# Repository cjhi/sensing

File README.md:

# Sensing

Repository for all Olin Rocketry hardware and firmware.

The purpose of the avionics system is to determine when to deploy the drogue and main chutes, and to send the signal to do so to the recovery system. The flight computer contains several sensors to help detect apogee, and a microcontroller to read and process the data and send the signal.

The avionics system consists of

- a commercial-off-the-shelf (COTS) flight computer;
- a student-designed flight computer, which includes sensors, microcontroller, GPS, and radio; and
- a student-designed battery management system (BMS).

The COTS computer is a **\_** model. It has its own batteries, sensors, and radio and can trigger the recovery system independently. It is intended as a backup and is required by IREC competition rules (partly so they have a reliable altitude measurement for the competition). The BMS is described on the Power Management subteam page. It can suppy a steady 3.3V current up to about 1000 mA to the student-designed flight computer board.

**The flight computer consists of a Teensy 3.6 microcontroller and various sensors.**

- The [Teensy 3.6](https://www.pjrc.com/teensy/card9a_rev1.pdf) is computationally powerful enough for complex data processing, has many interrupt pins, and many pins in general for connecting multiple sensors. It also has a built-in SD card reader. The decision to use it was made before the Fall 2020 semester; other options were considered and may be viable for future iterations. The main drawback of the Teensy 3.6 is its cost, at around $30. This makes having multiple prototypes very expensive, especially if we want to distribute copies to team members living in separate places.
- We considered 3 different inertial measurement units (IMUs, or accelerometers):
  - [ADXL345](https://www.analog.com/media/en/technical-documentation/data-sheets/ADXL345.pdf) is a very common 3-axis accelerometer. It is widely available and was already in stock from JLC, the company manufacturing our board. This means our boards will have the ADXL345 already populated when it is shipped to us, a bonus.
  - [BMI088](https://download.mikroe.com/documents/datasheets/BMI088_Datasheet.pdf) is a 6-axis accelerometer and gyroscope (axes 4-6 are angular acceleration).
  - [BNO055](https://cdn-shop.adafruit.com/datasheets/BST_BNO055_DS000_12.pdf) is a 9-axis accelerometer, relative, and absolute gyroscope (axes 7-9 are absolute orientation).

We designed our Rev1 PCB to hold all three IMUs, so that we could test all of them at once. However, as of ordering time in January, the BMI088 and BNO055 were out of stock at Digikey and Mouser, so these were never tested.

- [MPL3115A2](https://www.nxp.com/docs/en/data-sheet/MPL3115A2.pdf) is a barometer calibrated to provide altimetry. It is the most important sensor, as it allows us to determine our absolute altitude. Our simplest apogee detection is triggered by a certain number of consecutive decreasing altitude measurements.
- Header pins for the [Adafruit Ultimate GPS Breakout (Version 3)](https://www.adafruit.com/product/746?__hstc), a $40 complete GPS module.
- Header pins for the [RFM9X LoRa Packet Radio Breakout](https://learn.adafruit.com/adafruit-rfm69hcw-and-rfm96-rfm95-rfm98-lora-packet-padio-breakouts/arduino-wiring), the currenty preferred radio (see Communications subteam page).

**Rev 1 Testing Update: Spring 2021**

The sensors on Rev1 (the ADXL345 accelerometer and the MPL3115A2 barometer) work, and the data can be read over I2C. The current data format is a csv file with time since launch, x, y, and z acceleration, pressure, altitude, and temperature. The readings from the accelerometer have very little noise when at rest (the only test performed so far - others to follow soon). The barometer has some issues. First of all, it has an offset of about 1.7 atmospheres. When those 1.7 atm are subtracted out, however, it provides high precision and sensitivity. The altitude readings are off by the same offset, as I believe they are calculated from the barometer reading anyway. The temperature has some 20 degrees F offset and significant drift of 2-5 degrees F over a few minutes. More testing to follow.

I looked at the specs and realized that the ADXL345 and MPL3115A2 together consume less than 3 mA of current at their max. Since the Teensy can output 250 mA through those pins, I don’t see why to use an external power source; we can just use the 3.3V pins on the Teensy.
The tests I have done have been using the 3.3V pin as a power source.

**Tests performed 3/26/2021:**

**Power supply test:** Get an external power supply and give 3.3V to the power inputs. Test the test points and the Teensy’s Vin pin. Test data logging onto SD card. Test sensors connected only to external power supply vs. connected to Teensy 3.3V pin vs. connected to both.

**Results:**
The transistor part of the Rev1 power management circuit did not work. For some reason, there was always only ~0.6V on both the gate and drain pins, and so 0.6V on the rest of the PCB. I tried several pin configurations and nothing helped. It worked fine when I bypassed the transistor and powered 3.3V to both the Teensy and the PCB.
The Teensy could not write to the SD card when the PCB and Teensy were powered independently; it only works when the rest of the PCB is powered through the Teensy’s dedicated 3.3V pin. Therefore, I recommend just using the Teensy’s 3.3V pin to power the sensors.

In this case, I suggest the voltage supplied by the BMS should be 3.6V instead of 3.3V, so that the linear voltage regulator on the Teensy can effectively supply the 3.3V to the sensors. Voltage regulators necessariy have a small voltage drop across them, although I came across a [source](https://forum.pjrc.com/threads/55789-Power-Teensy-3-6-with-lipo-battery?p=203568&viewfull=1#post203568) that says the Teensy will bypass its voltage regulator if the voltage is too low, so there is not necessarily an issue.

**MPL3115A2 Accuracy Test:** Take the Rev1 board up and down the stairs of the MAC building 2 times and measure altitude difference.

**Results:**
The readings are inaccurate, yet very precise. The pressure has reads on the order of 200 kPa, which is double what is expected (1 atmosphere is about 100 kPa), and the temperature reads 90 degrees F in a 70 degree room. Yet after the offset is subtracted, the sensor tracks changes in height of less than 20 feet (the distance between floors in the MAC, and the highest resolution analyzed) quite well. The graph below shows the corrected elevation and temperature over the course of my trip up and down the stairs of the MAC, then outside onto the great lawn and up to the 4th floor of West Hall. There is some drift over time as it sat on my desk after “landing,” on the order of 20 feet over 20 minutes. This is worrying, but it will likely not be a problem during a launch lasting a few minutes.

**Developing the Rev 2 board**

With the ADXL345 and MPL3115A2 sensors confirmed to work, the main objective of the Rev 2 board is to make it fit into the avionics bay. The final board is 80mm tall by 72mm wide and has a mounting hole in each corner. The power supply transistor circuit has been replaced with a power multiplexer, a zener diode was added for overvoltage protection, and the power from the BMS goes directly into the Vin pin on the Teensy; the sensors and other circuitry are powered by the Teensy's 3.3V pin as discussed above. Additionally, 5 debugging LEDs, one power LED, and a [buzzer](https://www.digikey.com/en/products/detail/mallory-sonalert-products-inc/PT-1340P-P10-PQ/4996070) have also been added and are controlled by spare digital pins on the Teensy. A 10uF capacitor was added between the power and ground pins of the radio upon testing by the Communications team.

The board has been ordered from JLC and will arrive within a couple days.

## Guide to creating PCBs

**The process for creating the flight computer PCB has multiple stages:**
  1. Components are selected, including the microcontroller and sensors.
  2. Schematics are created for each sensor individually. This mainly involves copying the circuit diagram from the datasheets for each sensor. Every sensor needs at least two capacitors for its power source, and some require external pull-up resistors, for example. The BNO055 is connected to an external crystal oscillator. It’s also a good idea to add test points (basically large, labelled vias) for debugging purposes. We tried to add a test point to every trace on the schematic that would not be directly connected to the microcontroller (because we can access those traces directly through the microcontroller’s pins). 
  3. For the Rev1 board, footprints for the BNO055 and MPL3115A2 were created by copying the dimensions given by the datasheets. The other footprints were downloaded from snapeda.com. In reality, the only reason to create them manually is to get practice with KiCAD, which is why it was done this way for two of the sensors; in future, snapeda.com likely has all the footprints we will need, without the possibility of human error.*
  4. At this stage, layouts are also created for the supporting circuitry surrounding each sensor individually. These layouts will be manually recreated later, but it is easier to go through a few iterations to find the optimal footprint placements now, before all the layouts are combined on one board.
  5. Now, all of the individual schematics are moved into one place. This can be done in the KiCAD schematic editor (eeschema) by clicking File -> Append Schematic Sheet Content -> then navigate to the schematic to import and click Use Relative Path.
  6. Now all the schematics can be hooked up together; in this case it means connecting each sensor’s communication pins to the Teensy and power and ground to the power supply. A small circuit for regulating the power supply from the BMS, as well as header pins for the BMS and GPS and radio breakout boards are also added to this schematic.
  7. Review the schematics with the flight computer sub-team. Hopefully we have been checking in all along, but now is the last chance to make changes before a lot of work goes into the layout. After this, even small changes to the schematic can be very hard to implement in the layout without starting over.
  8. The layout of all the components for the final PCB is created. You cannot copy and paste the layouts created earlier for individual sensors, but you can follow the prior layouts as a guide. For the Rev1 board, we kept the components in the same relative orientation but did not pack them as closely together, to make debugging and potential fixes easier. During the layout process, it will probably make sense to swap the order of some pins connected to the microcontroller, in order to untangle the traces, or reduce the number of times traces have to cross over. Most pins on the Teensy 3.6 can function in the same way, so switching which pins are connected to which sensor is not a problem. Be careful not to switch the order of SCK and SDA; MISO and MOSI; or RX and TX; these pins are not interchangeable.
  9. It's a good idea to add filled zones on the front and back of the board. Having filled zones helps reduce signal noise and is standard practice. It also means there are fewer traces you have to draw. I usually make my filled zones be ground on both sides of the PCB, with an abundance of vias throughout the board to connect the front and back ground planes. Remember to press 'B' to redraw the zones in KiCAD.
  10. When the layout is done and reviewed, it is sent to JLC, our manufacturer. JLC can populate the PCB with basic components like capacitors, resistors, and even the ADXL345. They did not have any of the other sensors in stock, so we will solder those on campus. We will also solder header pins and large components like the power-regulating MOSFET transistor (which will be discontinued in Rev2).
  11. Next up is writing the firmware to test the sensors and hopefully getting some data!

\* In fact, I did make a very significant error while copying the footprint from the datasheet for both the BNO055 and the MPL3115. I copied the pads as they were shown in the datasheet, which was a bottom-up view. What matters for the layout is the top-down view (think about how the sensor sits on the PCB; you want to design the pads so they sit directly beneath the sensor). When you design the pads using the bottom-up view, you get a mirror image of how they are supposed to be. Moreover, since the footprints are often symmetrical, it can be impossible to tell you’ve made a mistake, until you realize that the pins things are supposed to be connected to are actually on the opposite side of the chip.

### Rev2 images

**Rev2 full schematic**

**Rev2 power supply**

**Rev2 layout**

**Rev2 3D model (front)**

**Rev2 3D model (back)**

### Rev1 images

**Rev1 full schematic**

**Rev1 power supply**

**Rev1 layout**

**Rev1 3D model (front)**

**Rev1 3D model (back)**

## Ordering PCBs From JLCPCB

For ordering the boards, go to JLCPCB.com (https://jlcpcb.com/RAT), and click on "Quote Now" button.

JLCPCB (ShenzhenJLC Electronics Co., Ltd.), is the largest PCB prototype enterprise in China, and a high-tech manufacturer specializing in quick PCB prototype and small-batch PCB production. You can order a minimum of 5 PCBs for just $2.

First: Upload the gerber files for the board by clicking the "Add gerber file" button. You’ll notice a message at the bottom if the file is successfully uploaded.

A correctly uploaded gerber folder renders the board as follows:

Second: In order to get the board assembled (optional, based on the project requirements), select the "SMT Assembly option. It is important to select the side of the PCB that needs to be assembled, as well as the quantity for SMT. Press the "Confirm" button, then press the "Next" button.

Third: upload the BOM (Bill of Material) and CPL (Component Placement List) files and click the "Next" button. It is necessary to make sure that each of these files follow the jlcpcb specified BOM and CPL formats, respectively:

- [Sample BOM](https://jlcpcb.com//video/JLCSMT_Sample_BOM1.xlsx?_ga=2.42560357.1905056644.1612161700-100444678.1610257845)
- [Sample CPL](https://jlcpcb.com//video/JLCSMT_Sample_CPL1.xlsx?_ga=2.42560357.1905056644.1612161700-100444678.1610257845)
- [SMT FAQ's](https://support.jlcpcb.com/category/78-smt-assembly?_ga=2.42560357.1905056644.1612161700-100444678.1610257845)

Note: If there is an issue with the BOM/CPL formatting, the the page will keep erroring out until it is resolved.

Fourth: The parts are automatically detected through the uploaded BOM. They are also matched against jlcpcb's in-stock parts. It is important to go through each row and confirm if the auto-detected parts are the desired parts. Some parts will remain undetected if they cannot be assembled through SMT and require manual assembly post-deilvery.

Fifth: The website renders an assembled board using the CPL file. This feature can be used to review the placement of the components (including orientation). Once carefull reviewed, the next step is to download a list of parts remaining to be assembled towards the bottom of this page view. It is important to place an order for the remaining components to be manually assembled upon delivery.

Sixth: Click on the “Save to Cart” button. Then, click on the "Secure Checkout" button.

Last: Add the payment details and choose the suitable delivery method (this includes FedEx, DHL, and standard mail options). Then, place the order.

Optional: To review the production status of the board, click on the "Order History" button under username. Then, click on In Production > view progress to obtain timestamps for each of the production steps in real time.

**Design Reviews**

-11/9/2022

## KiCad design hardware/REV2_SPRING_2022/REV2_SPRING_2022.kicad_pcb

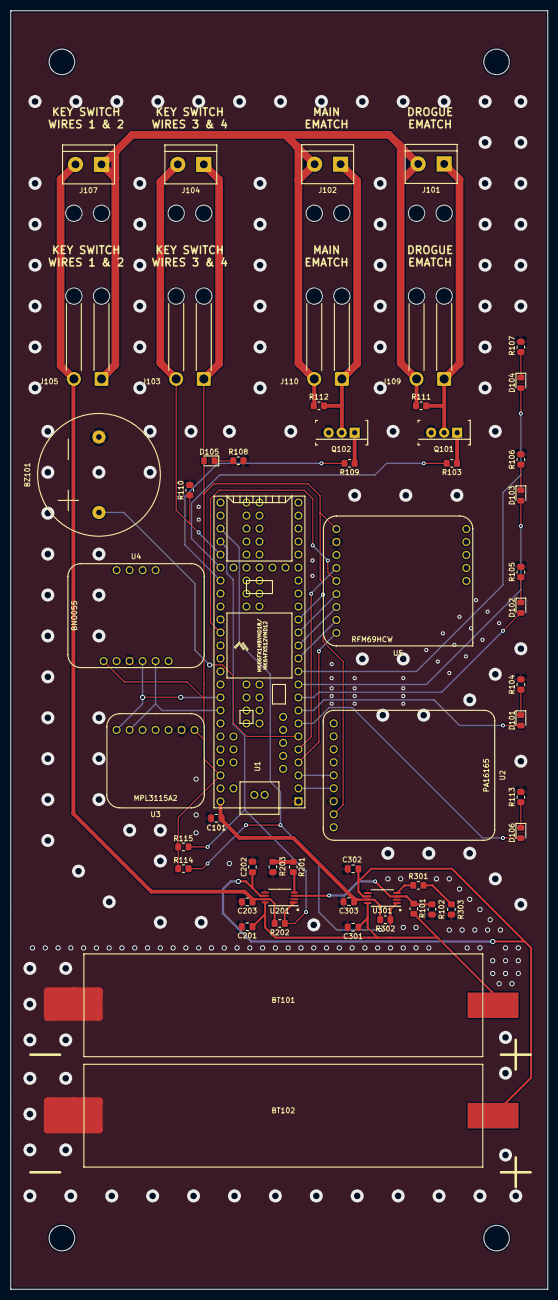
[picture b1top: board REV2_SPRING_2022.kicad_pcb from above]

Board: 2 copper layers, 105.0 x 250.0 mm, 54 parts (0 on the bottom side), 43 nets.

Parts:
BT101, BT102: Battery_Cell; MyBatteryHolder_MPD_BH-18650-PC2
BZ101: Buzzer; Large_Buzzer_24mmOD_14.8mmPinDistance_1.0mmPinDiameter
C101, C201, C202, C203, C301, C302, C303: C_0.1u; C_0805_2012Metric_Pad1.18x1.45mm_HandSolder
D101, D102, D103, D104, D105, D106: LED; LED_0805_2012Metric_Pad1.15x1.40mm_HandSolder
J101, J102, J104, J107: Screw_Terminal_01x02; TerminalBlock_bornier-2_P5.08mm
J103, J105, J109, J110: Conn_01x02_Female; SolderWire-1sqmm_1x02_P5.4mm_D1.4mm_OD2.7mm_Relief2x
Q101, Q102: Q_NMOS_GDS; TO-220-3
R101: R_15k; R_0805_2012Metric_Pad1.20x1.40mm_HandSolder
R102: R_4.7k; R_0805_2012Metric_Pad1.20x1.40mm_HandSolder
R103, R109, R110, R111, R112, R114, R115, R202, R302: R_10k; R_0805_2012Metric_Pad1.20x1.40mm_HandSolder
R104, R105, R106, R107, R108, R113: R_750; R_0805_2012Metric_Pad1.20x1.40mm_HandSolder
R201, R203, R301, R303: R_200; R_0805_2012Metric_Pad1.20x1.40mm_HandSolder
U1: Teensy3.6_All_Pins; Teensy35_36_All_Pins
U2: PA16165_Breakout
U3: MPL3115A2_Breakout
U4: BNO055_Breakout
U5: RFM69HCW_Breakout
U201, U301: TPS2113ADRBR; TSSOP-8_4.4x3mm_P0.65mm

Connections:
/3.3V: D105.2, J103.1, J104.1, R114.1, R115.1, U1.15, U1.51, U2.8, U3.1, U4.1, U5.1
/BAT1: BT101.1, C201.1, C301.1, R101.1, U201.8, U301.8
/BAT2: BT102.1, C202.1, C302.1, U201.6, U301.6
/BUZZER: BZ101.1, U1.6
/CS0: U1.12, U5.8
/E-MATCH_TRIGGER_1: R103.2, U1.35
/E-MATCH_TRIGGER_2: R109.2, U1.36
/EMATCH_1+: J101.1, J109.1, Q101.2, R111.2
/EMATCH_2+: J102.1, J110.1, Q102.2, R112.2
/KEY_SWITCH_DIGITAL: J103.2, J104.2, R110.1, U1.34
/LED_0: D106.2, U1.7
/LED_1: D101.2, U1.8
/LED_2: D102.2, U1.9
/LED_3: D103.2, U1.10
/LED_4: D104.2, U1.11
/MISO0: U1.14, U5.6
/MOSI0: U1.13, U5.7
/PWM: U1.4, U5.9
/RX1: U1.2, U2.6
/SCK: U1.40, U5.5
/SCL0: U1.46, U3.6, U4.5
/SCL2: U1.5, U5.4
/SDA0: U1.45, U3.7, U4.4
/TPS2113A for E-match/VSNS: R101.2, R102.1, U201.3, U301.3
/TPS_1_STAT: R114.2, R302.2, U1.32, U301.1
/TPS_2_STAT: R115.2, R202.2, U1.33, U201.1
/TX1: U1.3, U2.5
/V_EMATCH: J101.2, J102.2, J105.1, J107.1, J109.2, J110.2, R111.1, R112.1
/V_EMATCH_TO_KEY_SWITCH: C203.1, J105.2, J107.2, R202.1, U201.7
/V_TEENSY: C101.1, C303.1, R302.1, U1.53, U301.7
GND: BT101.2, BT102.2, BZ101.2, C101.2, C201.2, C202.2, C203.2, C301.2, C302.2, C303.2, Q101.3, Q102.3, R102.2, R104.2, R105.2, R106.2, R107.2, R108.2, R110.2, R113.2, R203.1, R303.1, U1.1, U1.39, U2.7, U3.2, U4.3, U5.2, U201.2, U201.5, U301.2, U301.5
unnamed: D101.1, R104.1
unnamed: D102.1, R105.1
unnamed: D103.1, R106.1
unnamed: D104.1, R107.1
unnamed: D105.1, R108.1
unnamed: D106.1, R113.1
unnamed: Q101.1, R103.1
unnamed: Q102.1, R109.1
unnamed: R201.1, R203.2
unnamed: R201.2, U201.4
unnamed: R301.1, R303.2
unnamed: R301.2, U301.4

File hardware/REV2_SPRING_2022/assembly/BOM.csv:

Comment,Designator,Footprint,LCSC Part #
C_0.1u,"C101, C201, C202, C203, C301, C302, C303, ",0805,C28233
LED,"D101, D102, D103, D104, D105, D106, ",0805,C2296
R_15k,"R101, ",0805,C17475
R_4.7k,"R102, ",0805,C17673
R_10k,"R103, R109, R110, R111, R112, R114, R115, R202, R302, ",0805,C17414
R_750,"R104, R105, R106, R107, R108, R113, ",0805,C17818
R_200,"R201, R203, R301, R303, ",0805,C17540

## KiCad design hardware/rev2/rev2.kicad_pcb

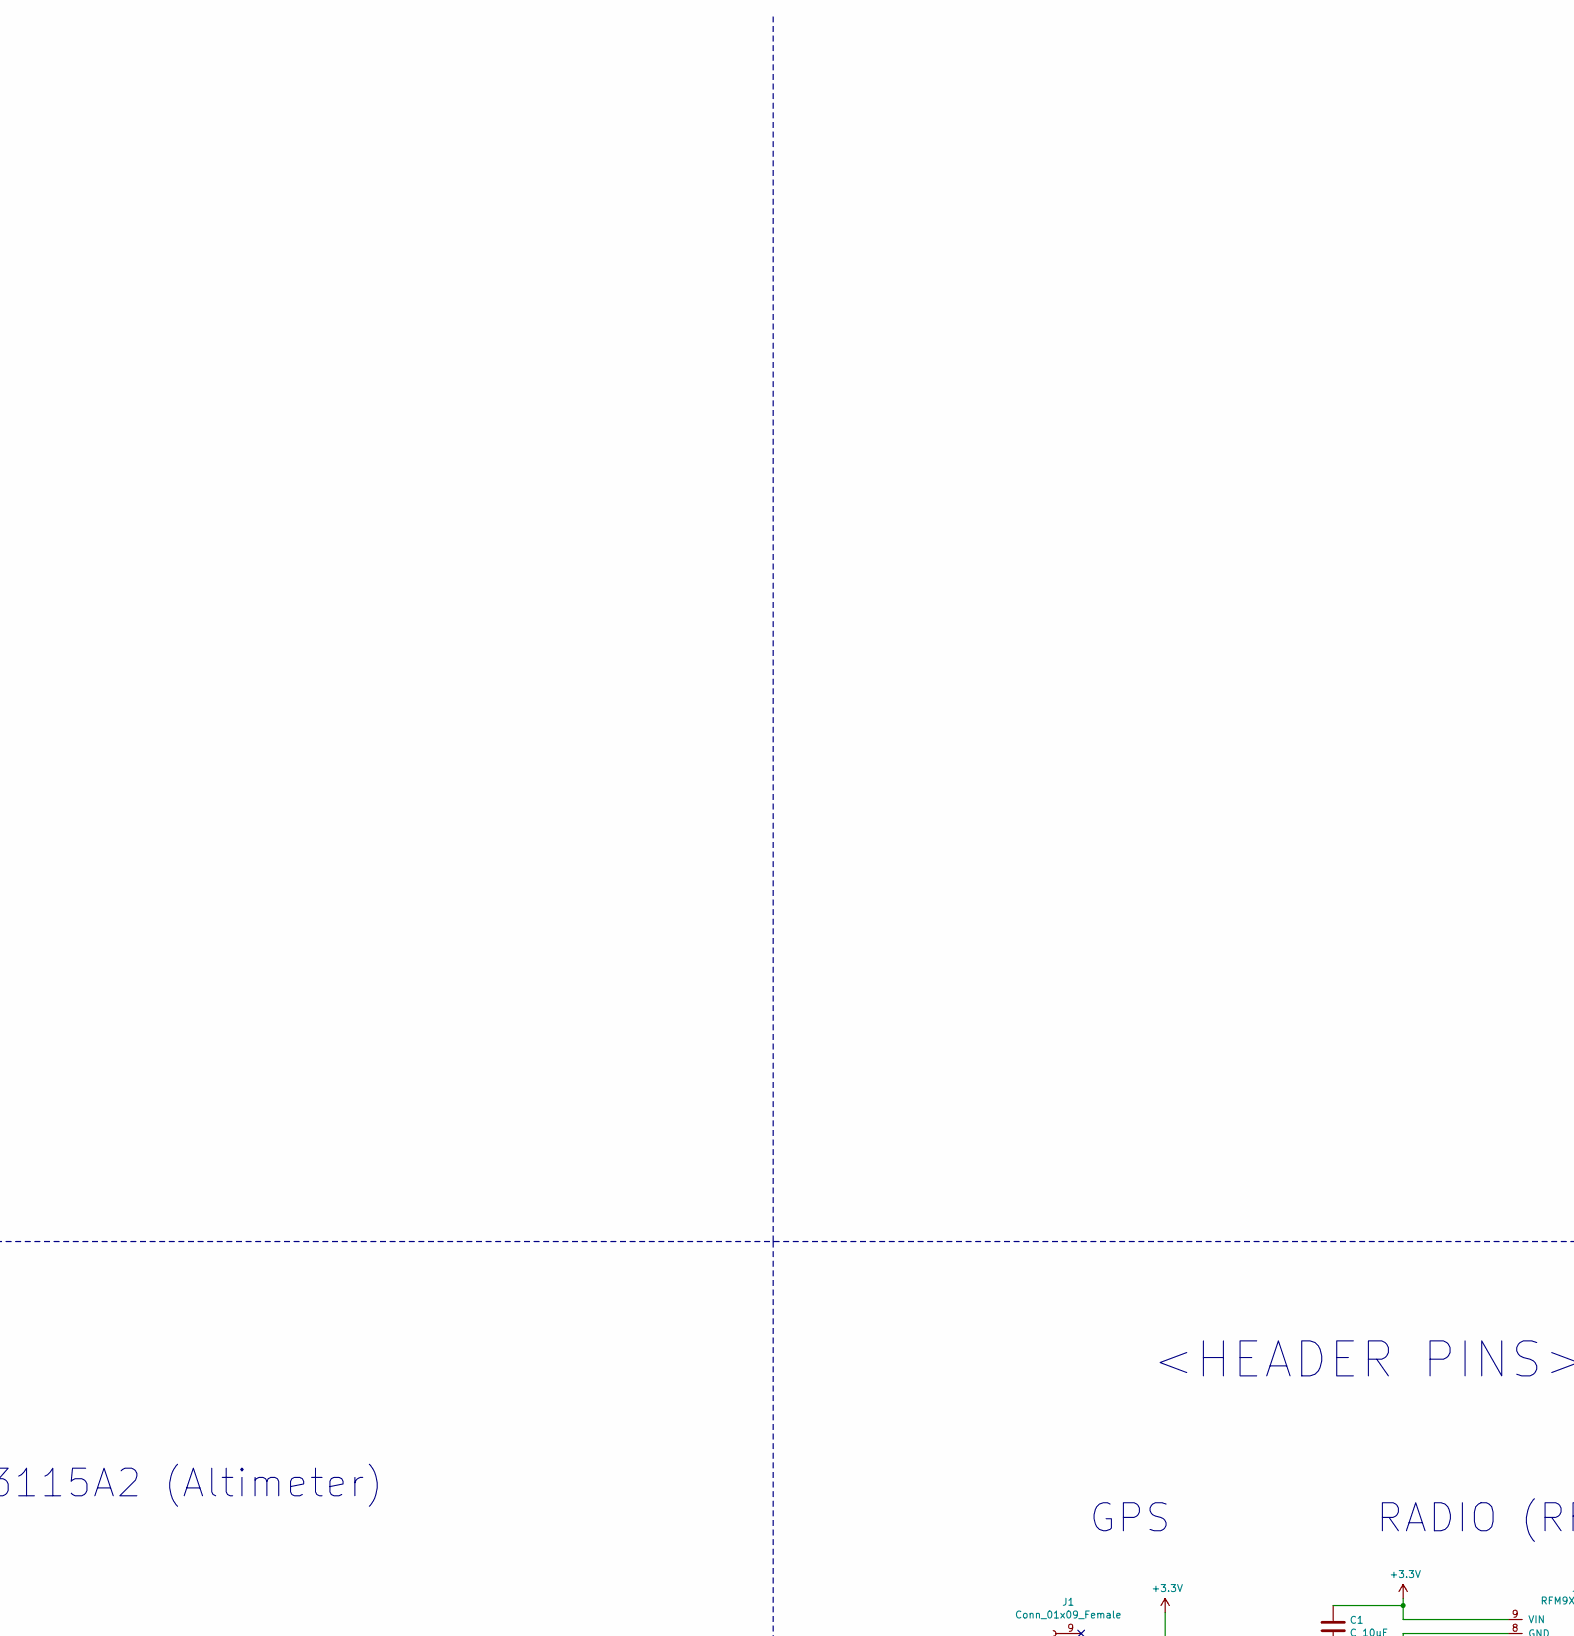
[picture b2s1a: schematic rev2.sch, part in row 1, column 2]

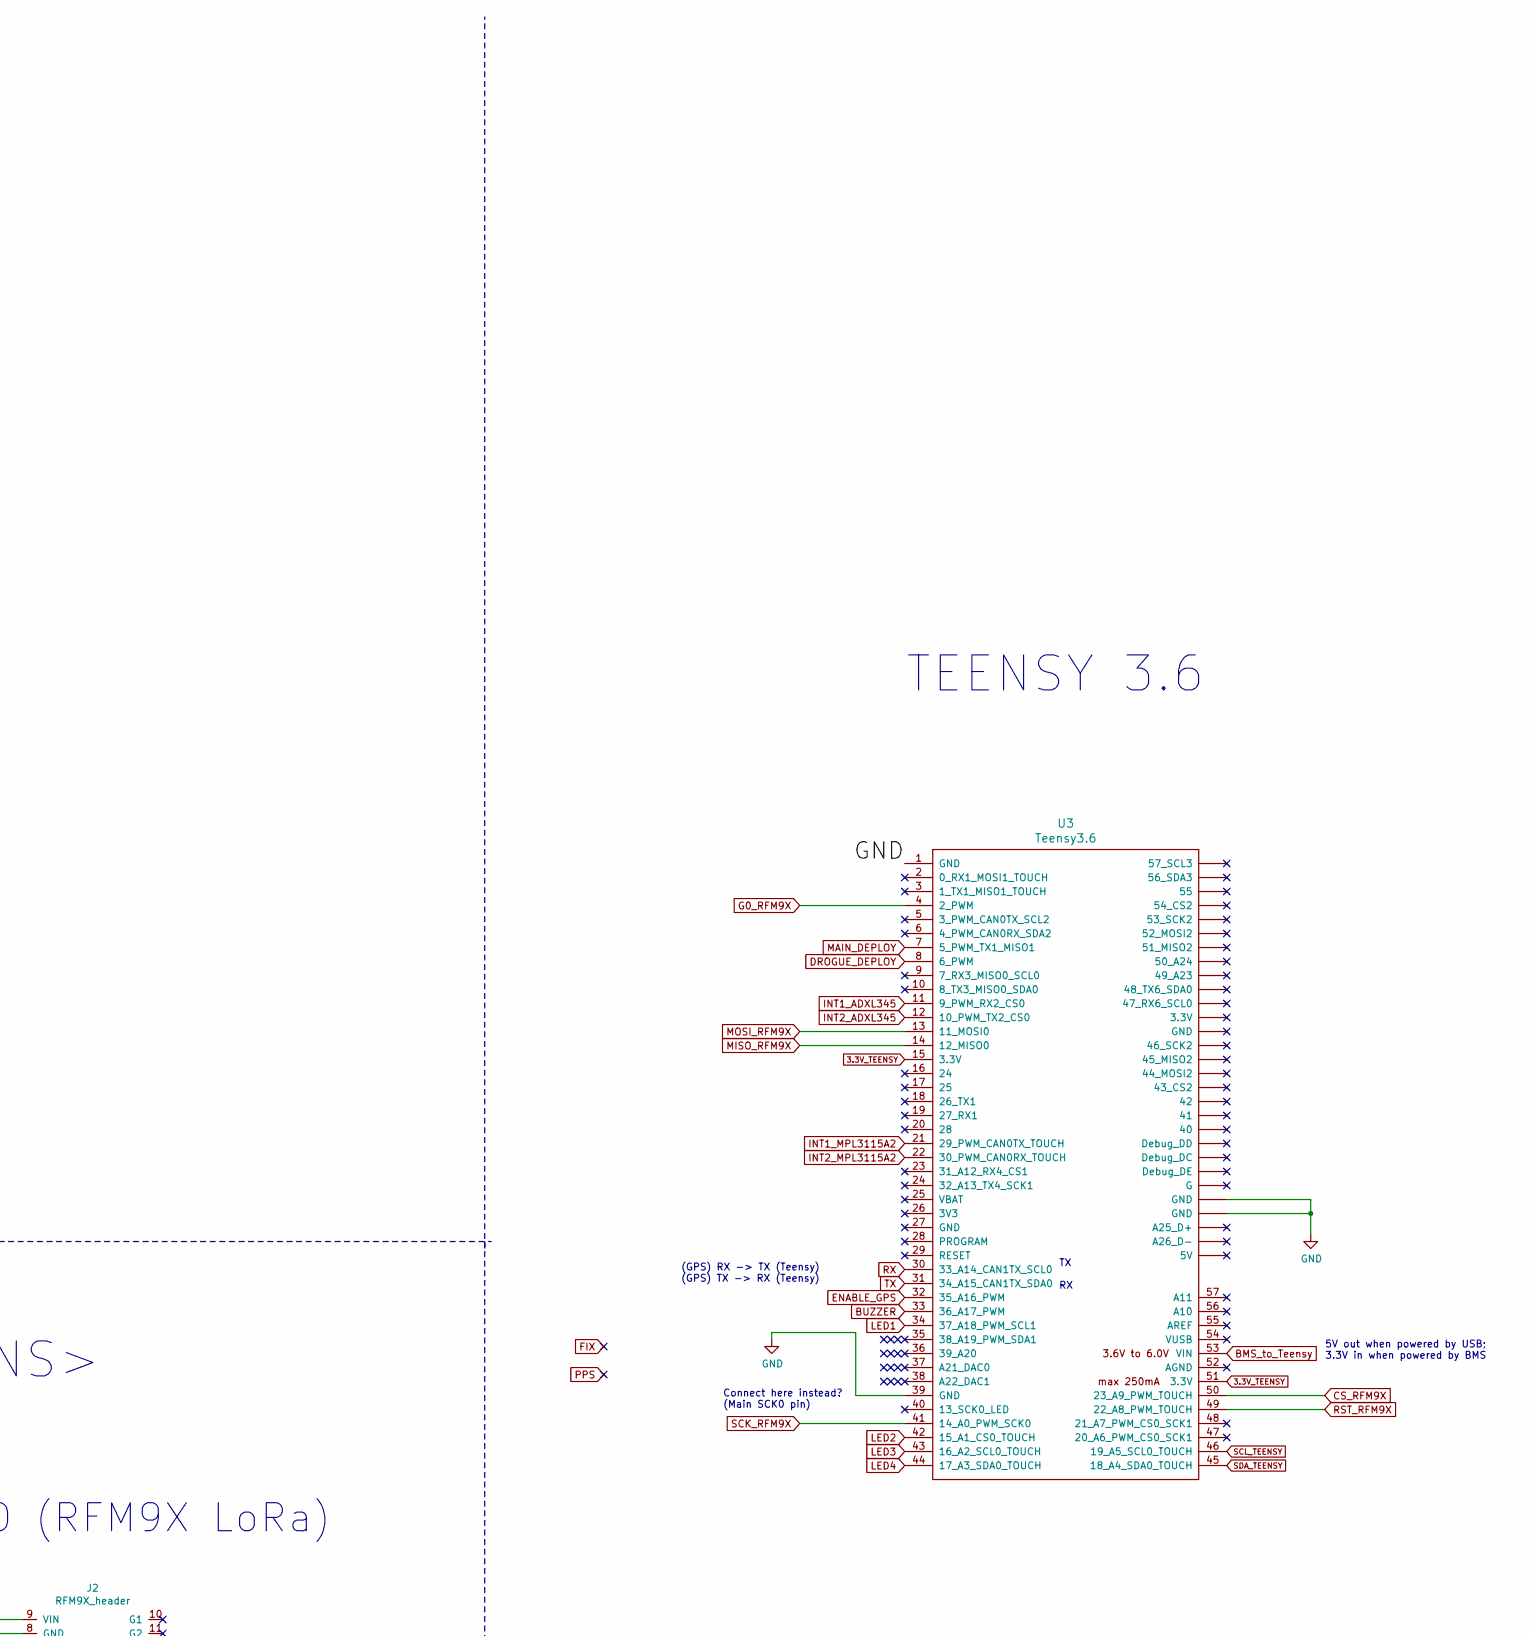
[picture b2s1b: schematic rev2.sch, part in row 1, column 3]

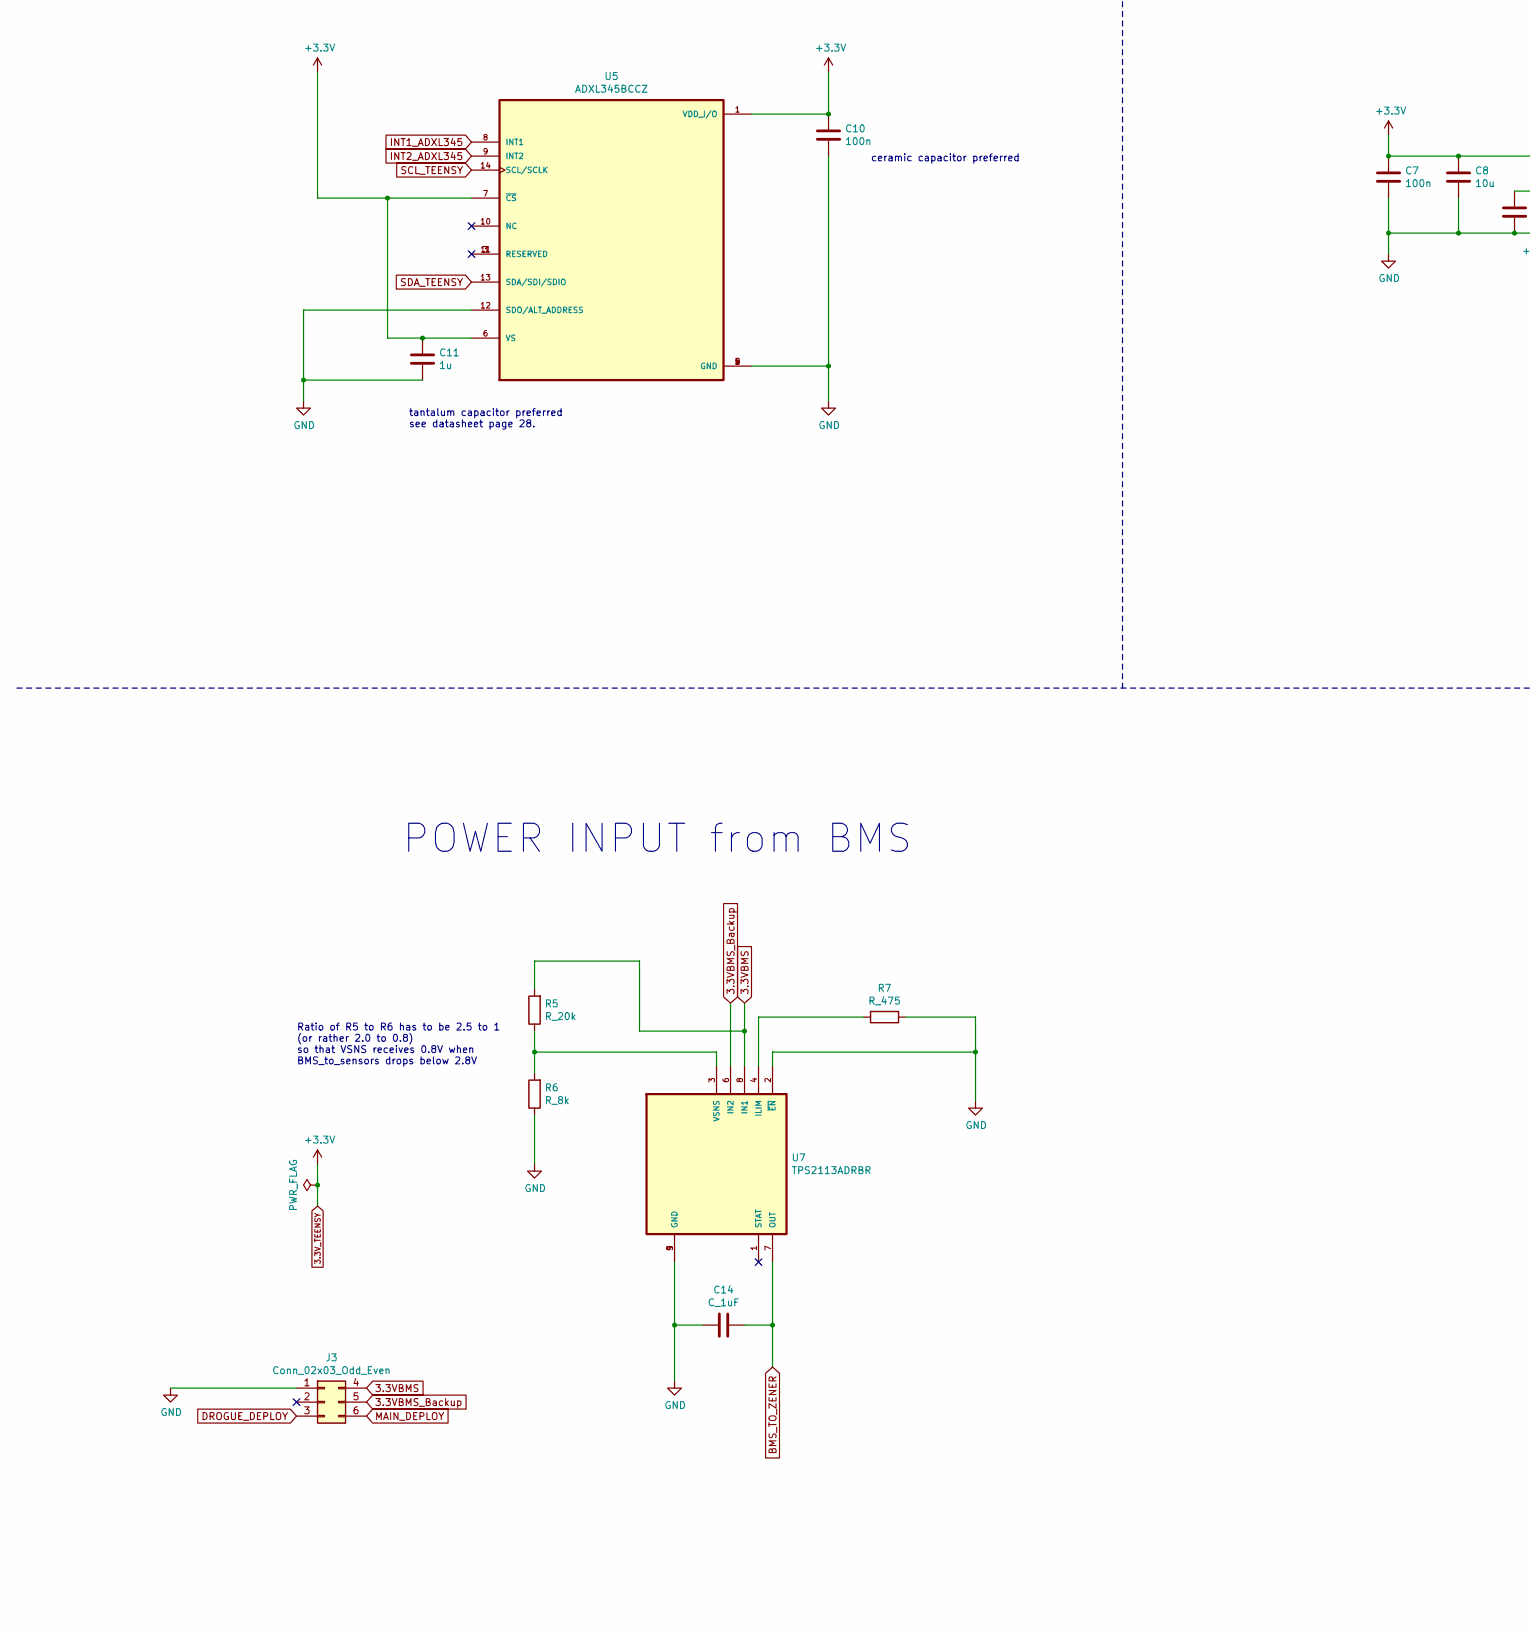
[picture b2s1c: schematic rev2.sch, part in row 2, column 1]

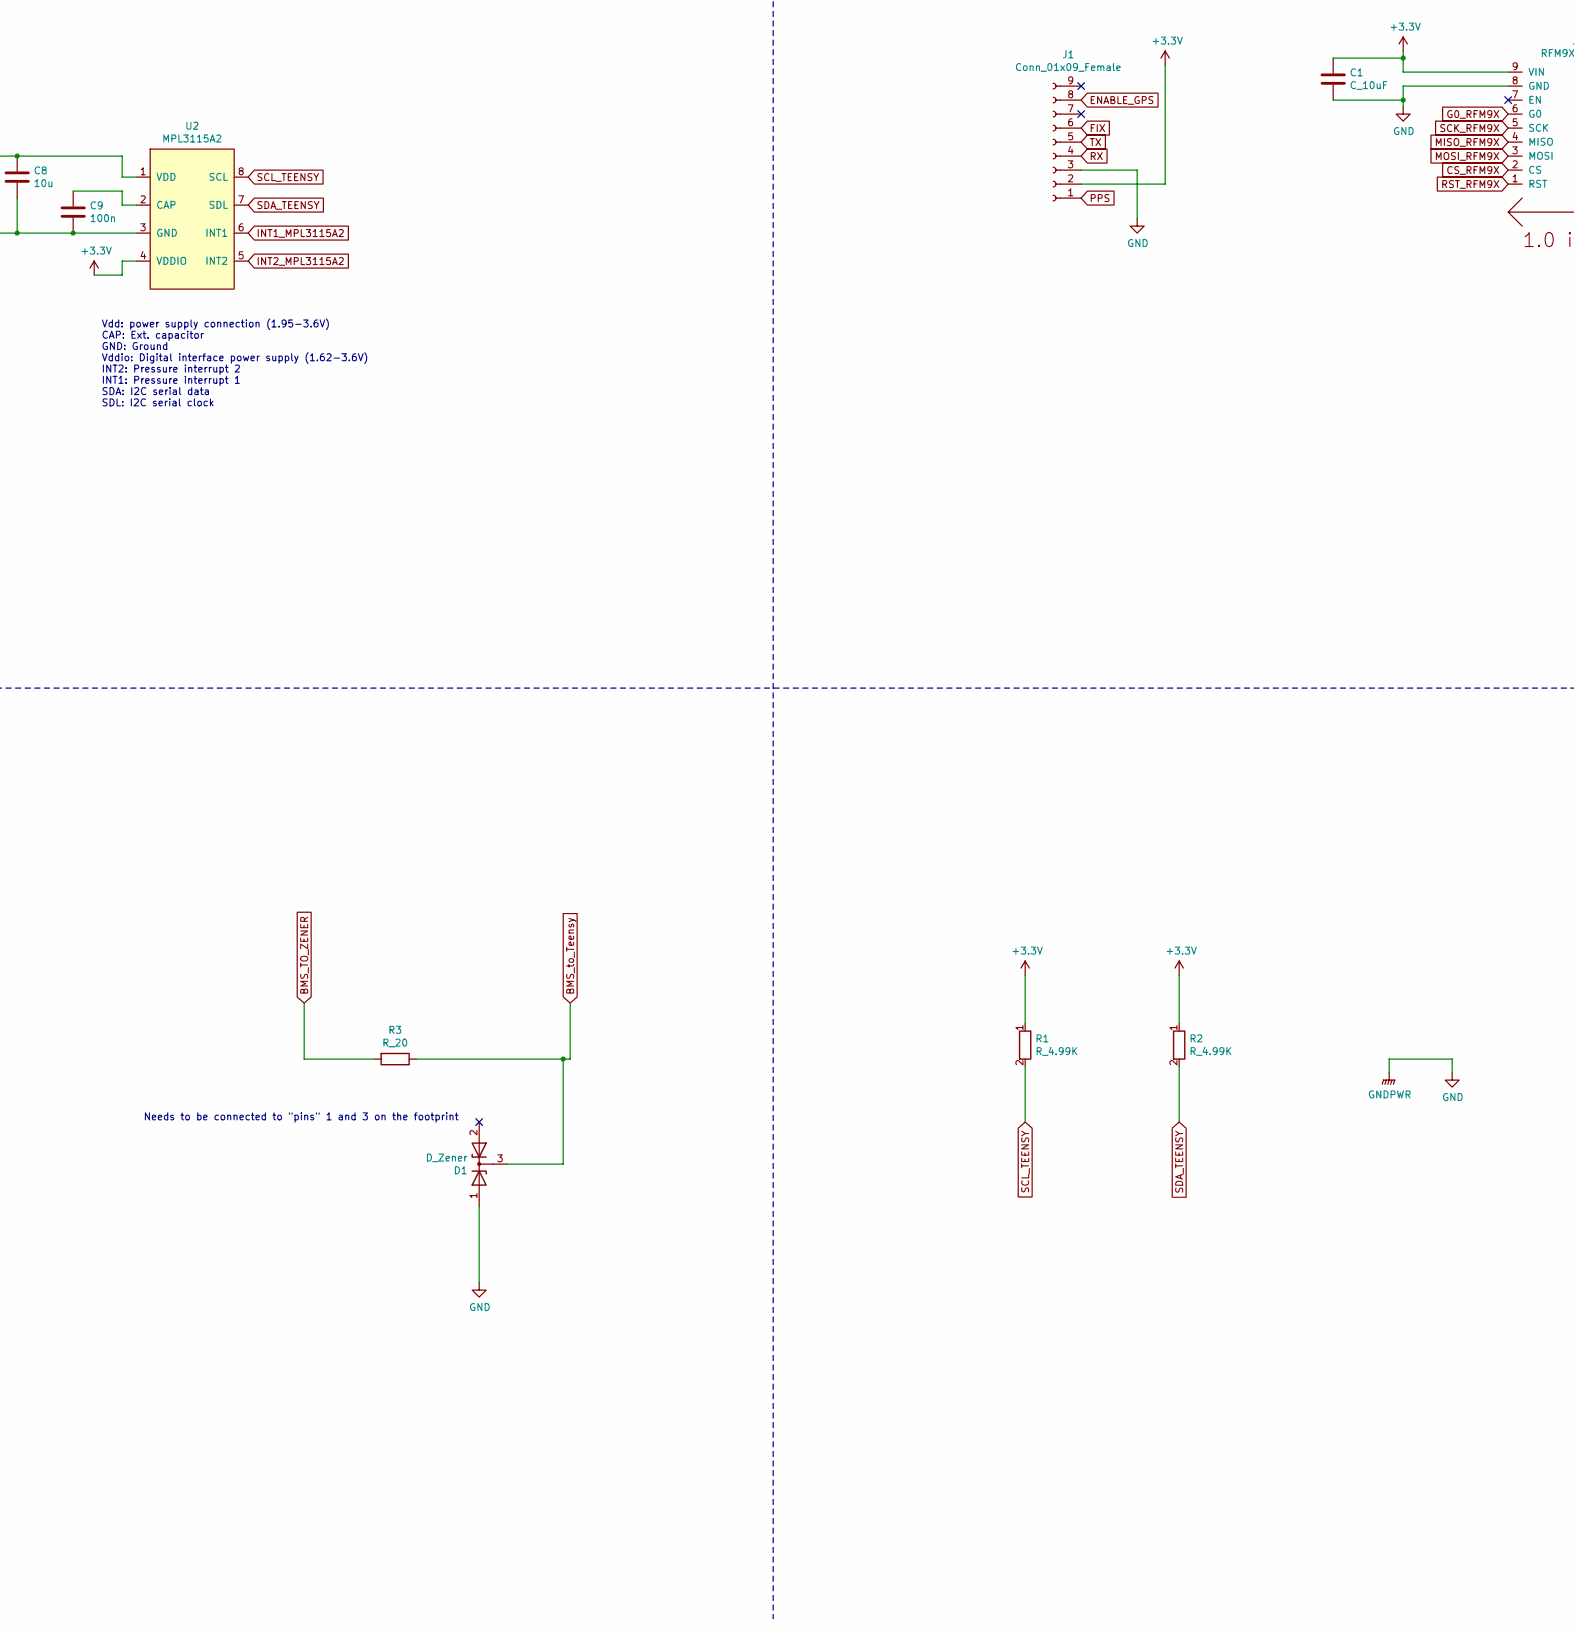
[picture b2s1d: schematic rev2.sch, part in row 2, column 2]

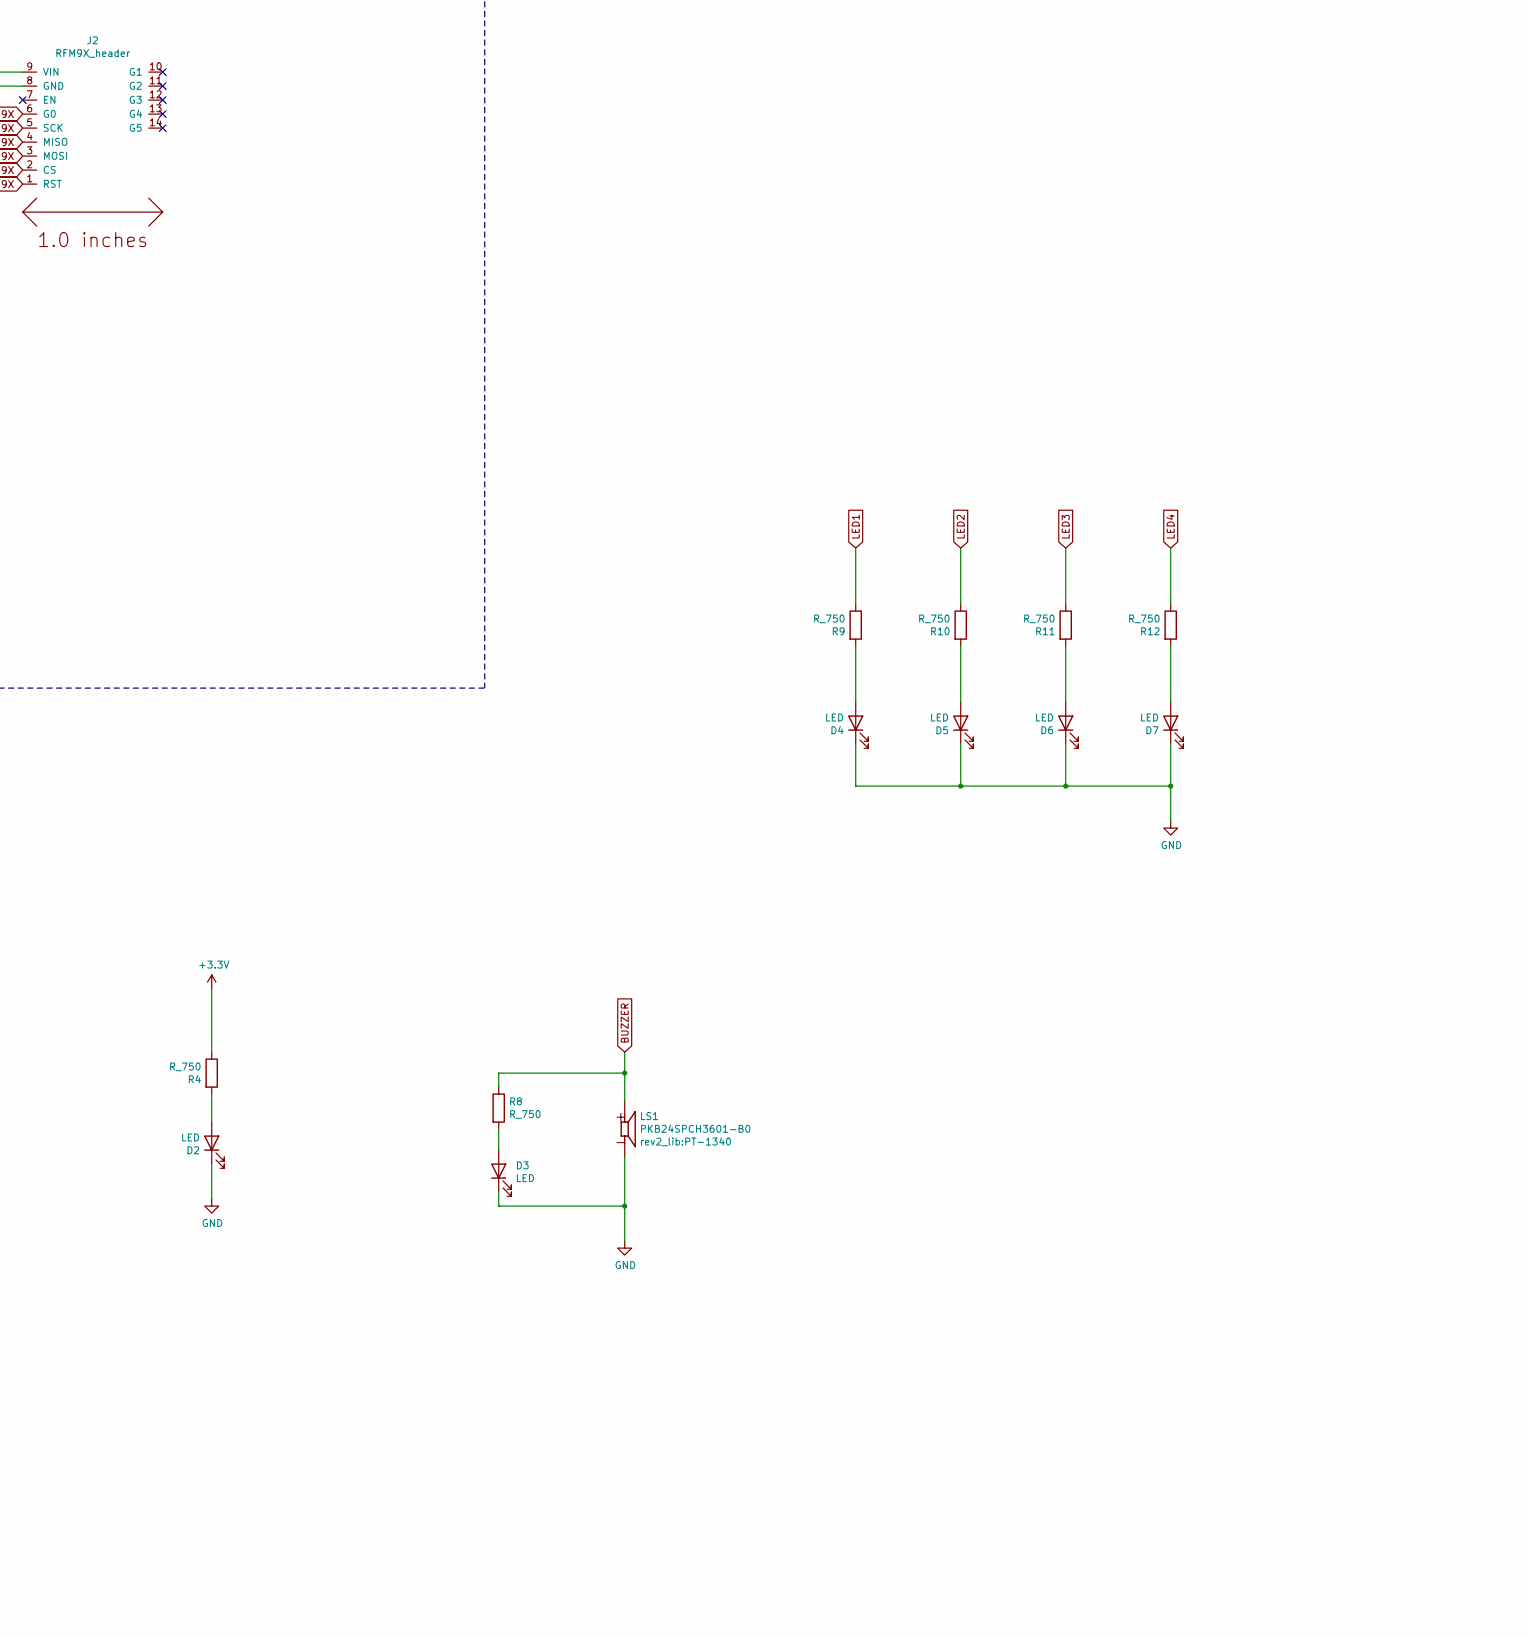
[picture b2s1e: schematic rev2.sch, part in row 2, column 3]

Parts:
C1: C_10uF; C_0805_OEM; MPN 1276-1052-1-ND
C7, C9: 100n; C_0805_OEM
C8: 10u; C_0805_OEM
C10: 100n; C_0805_OEM; MPN 478-3352-1-ND
C11: 1u; C_0805_OEM; MPN 1276-2887-1-ND
C14: C_1uF; C_0805_OEM; MPN 1276-2887-1-ND
D1: D_Zener; SOT-23
D2, D3, D4, D5, D6, D7: LED; AA3528LSECKT-J4
J1: Conn_01x09_Female; PinSocket_1x09_P2.54mm_Vertical
J2: RFM9X_header
J3: Conn_02x03_Odd_Even; Molex_Nano-Fit_105312-1106
LS1: PKB24SPCH3601-B0; PT-1340; PARTREV March 24, 2017
R1, R2: R_4.99K; R_0805_OEM
R3: R_20; R_0805_OEM
R4, R8, R9, R10, R11, R12: R_750; R_0805_OEM
R5: R_20k; R_0805_OEM; MPN 311-475CRCT-ND
R6: R_8k; R_0805_OEM; MPN 311-475CRCT-ND
R7: R_475; R_0805_OEM; MPN 311-475CRCT-ND
U2: MPL3115A2
U3: Teensy3.6; Teensy3-6
U5: ADXL345BCCZ; ADXL345
U7: TPS2113ADRBR

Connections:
3.3VBMS: J3.4, R5.2, U7.8 (IN1)
3.3VBMS_Backup: J3.5, U7.6 (IN2)
3.3V_TEENSY: C1.1, C7.1, C8.1, C10.1, C11.1, J1.2, J2.9 (VIN), R1.1, R2.1, R4.1, U2.1 (VDD), U2.4 (VDDIO), U3.15 (3.3V), U3.51 (3.3V), U5.1 (VDD_I/O), U5.6 (VS), U5.7 (~CS)
BMS_TO_ZENER: C14.1, R3.2, U7.7 (OUT)
BMS_to_Teensy: D1.3 (K), R3.1, U3.53 (VIN)
BUZZER: LS1.P, R8.1, U3.33 (36_A17_PWM)
CS_RFM9X: J2.2 (CS), U3.50 (23_A9_PWM_TOUCH)
DROGUE_DEPLOY: J3.3, U3.8 (6_PWM)
ENABLE_GPS: J1.8, U3.32 (35_A16_PWM)
FIX: J1.6
G0_RFM9X: J2.6 (G0), U3.4 (2_PWM)
GND: C1.2, C7.2, C8.2, C9.2, C10.2, C11.2, C14.2, D1.1 (A), D2.1 (K), D3.1 (K), D4.1 (K), D5.1 (K), D6.1 (K), D7.1 (K), J1.3, J2.8 (GND), J3.1, LS1.N, R6.1, R7.1, U2.3 (GND), U3.1 (GND), U3.39 (GND), U3.~ (3.3V), U5.2 (GND), U5.4 (GND), U5.5 (GND), U5.12 (SDO/ALT_ADDRESS), U7.2 (~EN), U7.5 (GND), U7.9 (GND)
INT1_ADXL345: U3.11 (9_PWM_RX2_CS0), U5.8 (INT1)
INT1_MPL3115A2: U2.6 (INT1), U3.21 (29_PWM_CAN0TX_TOUCH)
INT2_ADXL345: U3.12 (10_PWM_TX2_CS0), U5.9 (INT2)
INT2_MPL3115A2: U2.5 (INT2), U3.22 (30_PWM_CAN0RX_TOUCH)
LED1: R9.1, U3.34 (37_A18_PWM_SCL1)
LED2: R10.1, U3.42 (15_A1_CS0_TOUCH)
LED3: R11.1, U3.43 (16_A2_SCL0_TOUCH)
LED4: R12.1, U3.44 (17_A3_SDA0_TOUCH)
MAIN_DEPLOY: J3.6, U3.7 (5_PWM_TX1_MISO1)
MISO_RFM9X: J2.4 (MISO), U3.14 (12_MISO0)
MOSI_RFM9X: J2.3 (MOSI), U3.13 (11_MOSI0)
unnamed: C9.1, U2.2 (CAP)
unnamed: D2.2 (A), R4.2
unnamed: D3.2 (A), R8.2
unnamed: D4.2 (A), R9.2
unnamed: D5.2 (A), R10.2
unnamed: D6.2 (A), R11.2
unnamed: D7.2 (A), R12.2
unnamed: R5.1, R6.2, U7.3 (VSNS)
unnamed: R7.2, U7.4 (ILIM)
unnamed: U5.3 (RESERVED), U5.11 (RESERVED)
PPS: J1.1
RST_RFM9X: J2.1 (RST), U3.49 (22_A8_PWM_TOUCH)
RX: J1.4, U3.30 (33_A14_CAN1TX_SCL0)
SCK_RFM9X: J2.5 (SCK), U3.41 (14_A0_PWM_SCK0)
SCL_TEENSY: R1.2, U2.8 (SCL), U3.46 (19_A5_SCL0_TOUCH), U5.14 (SCL/SCLK)
SDA_TEENSY: R2.2, U2.7 (SDL), U3.45 (18_A4_SDA0_TOUCH), U5.13 (SDA/SDI/SDIO)
TX: J1.5, U3.31 (34_A15_CAN1TX_SDA0)

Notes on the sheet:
MPL3115A2 (Altimeter)
Vdd: power supply connection (1.95-3.6V) CAP: Ext. capacitor GND: Ground Vddio: Digital interface power supply (1.62-3.6V) INT2: Pressure interrupt 2 INT1: Pressure interrupt 1 SDA: I2C serial data SDL: I2C serial clock
Pull-up resistors exist on another part of the schematic.
ADXL345
RADIO (RFM9X LoRa)
POWER INPUT from BMS
GPS
ceramic capacitor preferred
tantalum capacitor preferred see datasheet page 28.
TX RX
(GPS) RX -> TX (Teensy) (GPS) TX -> RX (Teensy)
5V out when powered by USB; 3.3V in when powered by BMS
<HEADER PINS>
TEENSY 3.6
Ratio of R5 to R6 has to be 2.5 to 1 (or rather 2.0 to 0.8) so that VSNS receives 0.8V when BMS_to_sensors drops below 2.8V
Needs to be connected to "pins" 1 and 3 on the footprint
Connect here instead? (Main SCK0 pin)

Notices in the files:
parts and their libraries:
Copyright 2016 Accelerated Designs. All rights reserved.
